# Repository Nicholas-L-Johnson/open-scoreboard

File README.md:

## Open Scoreboard

This project is a pocket scoreboard with Android/iOS/WatchOS apps.

The goal is a mass market product.  It beats out the existing devices on the market in features and price.

It really is small enough to fit in a pocket, and the battery lasts for up to 2 days of continuuous display on one charge.

It has some other modes too, a countdown timer and alarm clock

This project may be slightly doomed.  It will take about 35K to get the certifications, testing, and llc up to the level where these can be sold.  The real killer is the massive fee to use bluetooth.

I could seek a loan, but I am pretty against that at this point.  The app is not nearly ready, and it definitly needs to be migrated to a 4 layer board if I want to pass FCC testing.

Anyway, I'll keep working and maybe when it's ready there will be some cash I can spare on it.

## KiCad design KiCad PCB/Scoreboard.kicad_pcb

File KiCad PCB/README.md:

## PCB files

These are the hardware design files for the open scoreboard project.

The current design is based off of an nRF52833 with an RGB LED grid laid out as a scoreboard.

Version 0.1 controlled the LED's directly.  
This worked but required many pins and led to flickering and ghosting and lacked some creature comforts such as recharchable battery. 4 LEDs per segment also did not look great.

Version 0.2 attepted to switch to WLEDs.
This pulled far too much current and created heat problems. Battery charging and the larger NFC antenna were a success though.

The current version, 0.3 goes back to normal LEDs, but passes the control off to an LED grid controller. With lipo battery, improved NFC, Piezo, USB, 5 LED segments, and lower part count.

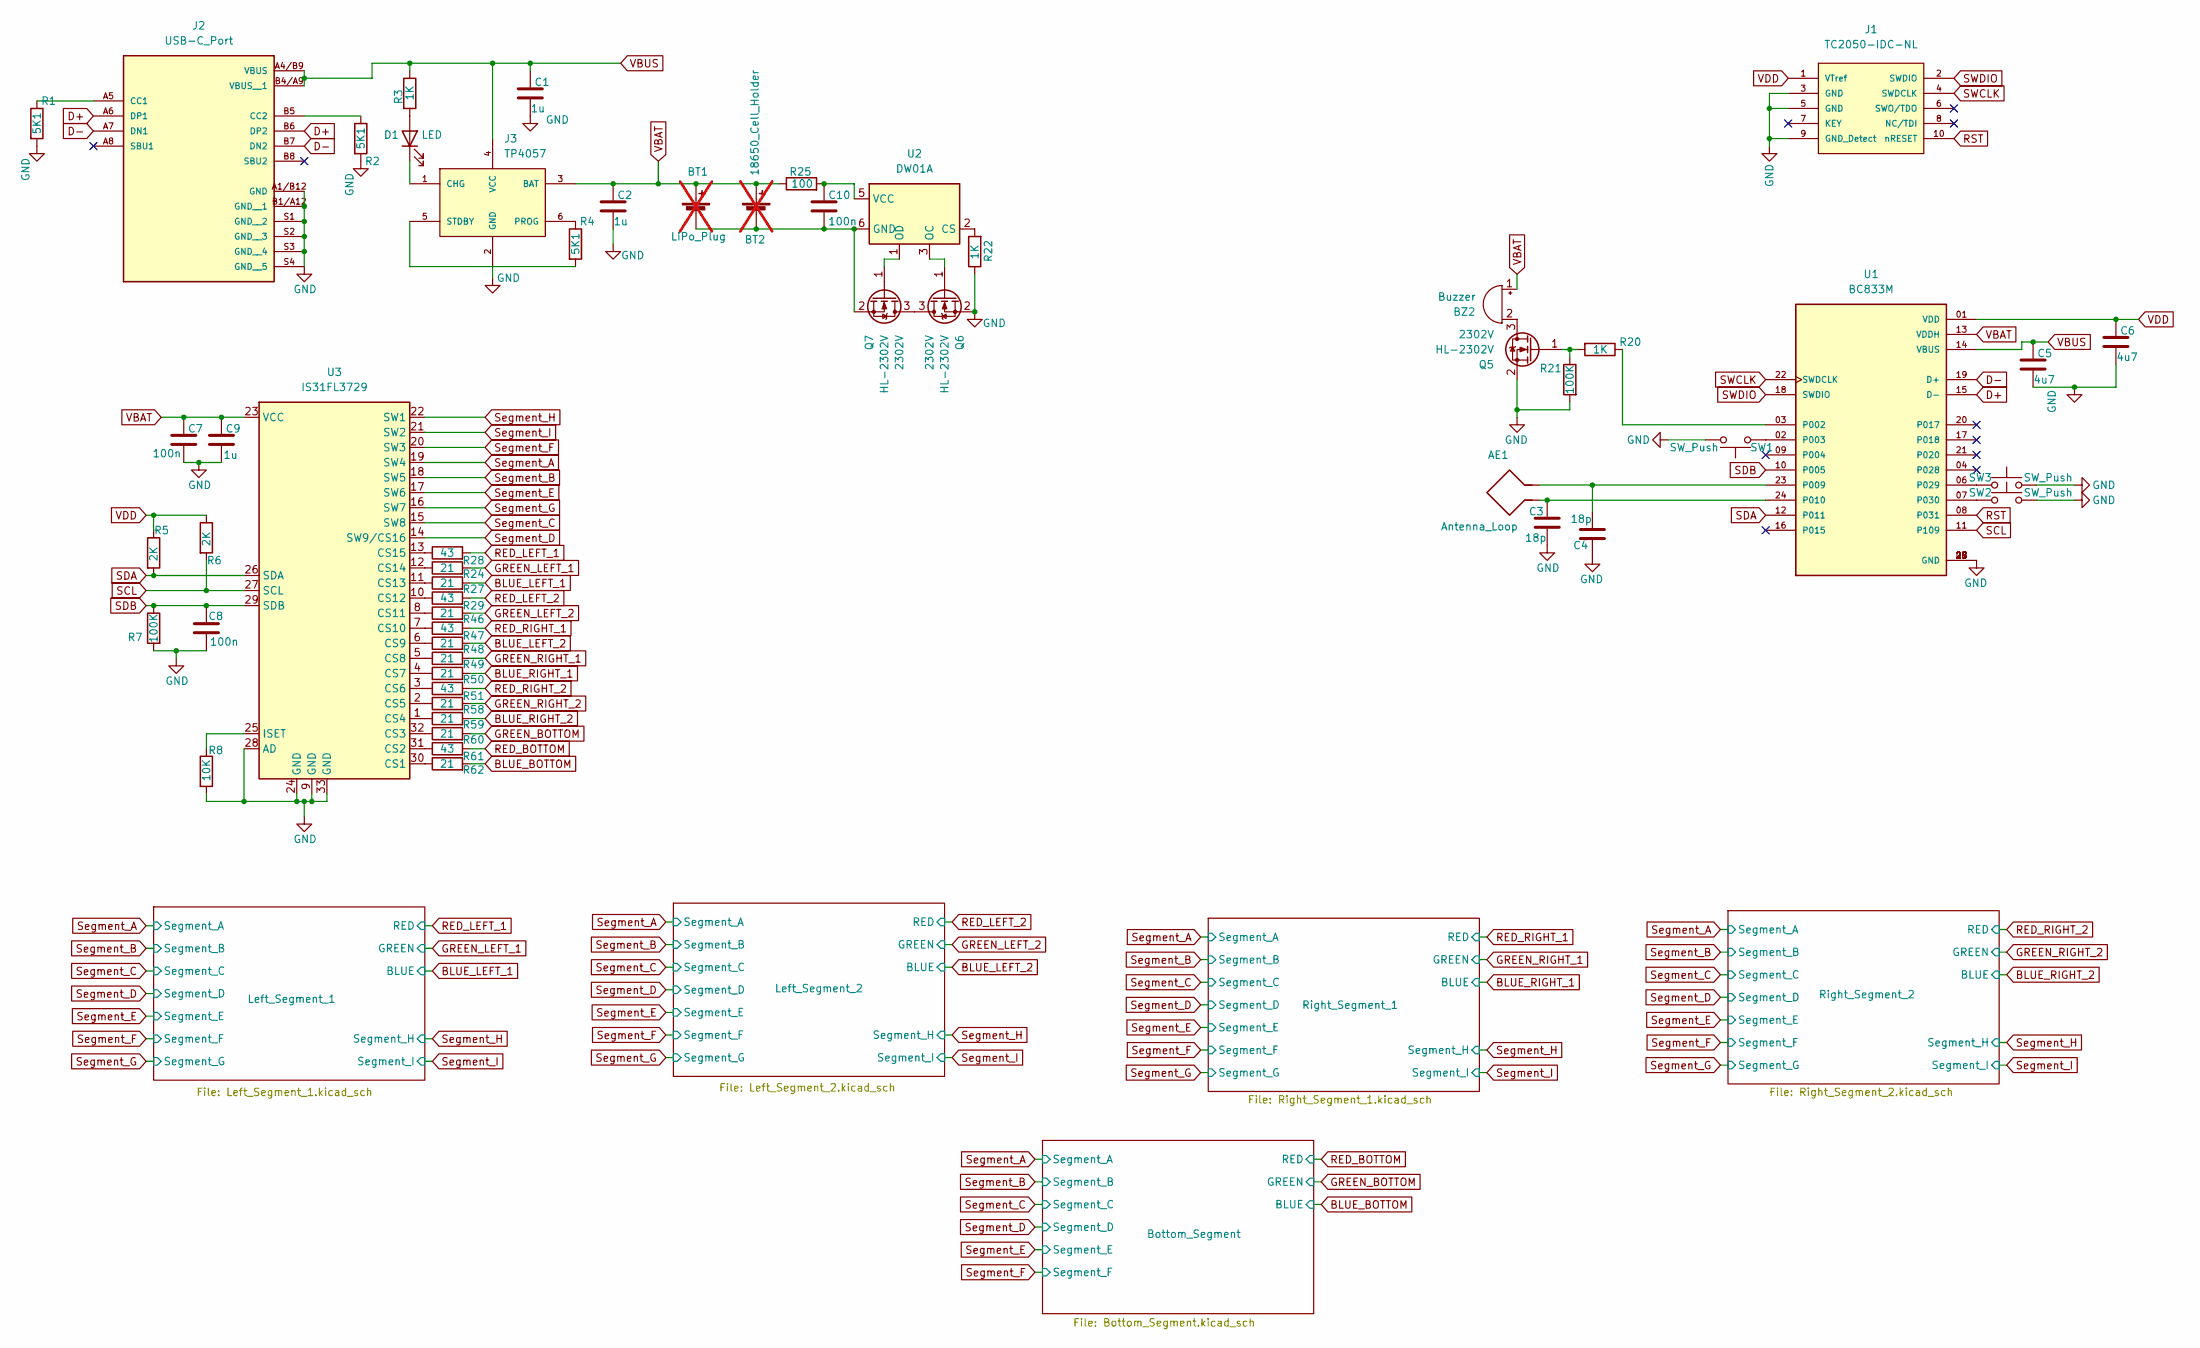
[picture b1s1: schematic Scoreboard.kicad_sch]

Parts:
AE1: Antenna_Loop; HM-NFC-Class3-Antenna
BT1: LiPo_Plug; JST_PH_S2B-PH-K_1x02_P2.00mm_Horizontal; Part Number WAFER-PH2.0-2PWB; LCSC Part Number C3029440; not fitted
BT2: 18650_Cell_Holder; Part Number BH-18650-A1AJ005; LCSC Part Number C5290176; not fitted
BZ2: Buzzer; XDCR_CMT-7525-80-SMT-TR; Part Number KLJ-7525-3627; LCSC Part Number C189208
C1, C2, C9: 1u; C_0603_1608Metric; Part Number CL10A105KO8NNNC; LCSC Part Number C1592
C3, C4: 18p; C_0603_1608Metric; Part Number FCC0603N180J500CT; LCSC Part Number C5137620
C5, C6: 4u7; C_0603_1608Metric; Part Number CGA0603X5R475K6R3JT; LCSC Part Number C7503506
C7, C8, C10: 100n; C_0603_1608Metric; Part Number CL10B104KA8NNNC; LCSC Part Number C1590
D1: LED; LED_0603_1608Metric; Part Number XL-1608SURC-06; LCSC Part Number C965799
J1: TC2050-IDC-NL; TAG-CONNECT_TC2050-IDC-NL; Part Number TC2050-IDC
J2: USB-C_Port; GCT_USB4110GFA; Part Number GT-USB-7014A; LCSC Part Number C963371
J3: TP4057; SOT-23-6; Part Number TP4057; LCSC Part Number C20199358
Q5, Q6, Q7: HL-2302V; SOT-23; Part Number 2302V; LCSC Part Number C7431443
R1, R2, R4: 5K1; R_0603_1608Metric; Part Number RC0603FR-075K1L; LCSC Part Number C105580
R3, R20, R22: 1K; R_0603_1608Metric; Part Number FRC0603J102 TS; LCSC Part Number C2907113
R5, R6: 2K; R_0603_1608Metric; Part Number FRC0603J202 TS; LCSC Part Number C2907137
R7, R21: 100K; R_0603_1608Metric; Part Number FRC0603J104 TS; LCSC Part Number C2907088
R8: 10K; R_0603_1608Metric; Part Number FRC0603J103 TS; LCSC Part Number C2930027
R24, R27, R46, R48, R49, R50, R58, R59, R60, R62: 21; R_0603_1608Metric; Part Number FRC0603F21R0TS; LCSC Part Number C5713281
R25: 100; R_0603_1608Metric; Part Number FRC0603J101 TS; LCSC Part Number C2907089
R28, R29, R47, R51, R61: 43; R_0603_1608Metric; Part Number FRC0603F43R0TS; LCSC Part Number C2907039
SW1, SW2, SW3: SW_Push; SW4_1437565_TEC; Part Number TS-1187A-C-D-B; LCSC Part Number C318888
U1: BC833M; XCVR_BC833M; Part Number BC833M
U2: DW01A; SOT-23-6; Part Number DW01A; LCSC Part Number C42380662
U3: IS31FL3729; QFN-32-1EP_4x4mm_P0.4mm_EP2.9x2.9mm_ThermalVias; Part Number IS31FL3729-QFLS4-TR; LCSC Part Number C2940549

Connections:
BLUE_BOTTOM: R62.2; also elsewhere on the board
BLUE_LEFT_1: R27.2; also elsewhere on the board
BLUE_LEFT_2: R48.2; also elsewhere on the board
BLUE_RIGHT_1: R50.2; also elsewhere on the board
BLUE_RIGHT_2: R59.2; also elsewhere on the board
D+: J2.A6 (DP1), J2.B6 (DP2), U1.15 (D-)
D-: J2.A7 (DN1), J2.B7 (DN2), U1.19 (D+)
GND: C1.2, C2.2, C3.2, C4.1, C5.2, C6.2, C7.2, C8.2, C9.2, J1.3 (GND), J1.5 (GND), J1.9 (GND_Detect), J2.A1/B12 (GND), J2.B1/A12 (GND__1), J2.S1 (GND__2), J2.S2 (GND__3), J2.S3 (GND__4), J2.S4 (GND__5), J3.2 (GND), Q5.2 (S), Q6.2 (S), R1.2, R2.2, R7.2, R8.2, R21.2, R22.1, SW1.1, SW2.1, SW3.1, U1.05 (GND), U1.25 (GND), U1.26 (GND), U1.27 (GND), U1.28 (GND), U3.9 (GND), U3.24 (GND), U3.28 (AD), U3.33 (GND)
GREEN_BOTTOM: R60.2; also elsewhere on the board
GREEN_LEFT_1: R24.2; also elsewhere on the board
GREEN_LEFT_2: R46.2; also elsewhere on the board
GREEN_RIGHT_1: R49.2; also elsewhere on the board
GREEN_RIGHT_2: R58.2; also elsewhere on the board
unnamed: BT1.2 (-), BT2.2 (-), C10.2, Q7.2 (S), U2.6 (GND)
unnamed: BZ2.2 (-), Q5.3 (D)
unnamed: D1.2 (A), R3.2
unnamed: D1.1 (K), J3.1 (CHG)
unnamed: J2.A5 (CC1), R1.1
unnamed: J2.B5 (CC2), R2.1
unnamed: J3.6 (PROG), R4.1
unnamed: J3.5 (STDBY), R4.2
unnamed: Q5.1 (G), R20.2, R21.1
unnamed: Q6.3 (D), Q7.3 (D)
unnamed: Q6.1 (G), U2.3 (OC)
unnamed: Q7.1 (G), U2.1 (OD)
unnamed: R20.1, U1.03 (P002)
unnamed: SW1.2, U1.02 (P003)
unnamed: AE1.2, C4.2, U1.23 (P009)
unnamed: AE1.1, C3.1, U1.24 (P010)
unnamed: SW3.2, U1.06 (P029)
unnamed: SW2.2, U1.07 (P030)
unnamed: R22.2, U2.2 (CS)
unnamed: C10.1, R25.2, U2.5 (VCC)
unnamed: R62.1, U3.30 (CS1)
unnamed: R61.1, U3.31 (CS2)
unnamed: R60.1, U3.32 (CS3)
unnamed: R59.1, U3.1 (CS4)
unnamed: R58.1, U3.2 (CS5)
unnamed: R51.1, U3.3 (CS6)
unnamed: R50.1, U3.4 (CS7)
unnamed: R49.1, U3.5 (CS8)
unnamed: R48.1, U3.6 (CS9)
unnamed: R47.1, U3.7 (CS10)
unnamed: R46.1, U3.8 (CS11)
unnamed: R29.1, U3.10 (CS12)
unnamed: R27.1, U3.11 (CS13)
unnamed: R24.1, U3.12 (CS14)
unnamed: R28.1, U3.13 (CS15)
unnamed: R8.1, U3.25 (ISET)
RED_BOTTOM: R61.2; also elsewhere on the board
RED_LEFT_1: R28.2; also elsewhere on the board
RED_LEFT_2: R29.2; also elsewhere on the board
RED_RIGHT_1: R47.2; also elsewhere on the board
RED_RIGHT_2: R51.2; also elsewhere on the board
RST: J1.10 (nRESET), U1.08 (P031)
SCL: R6.2, U1.11 (P109), U3.27 (SCL)
SDA: R5.2, U1.12 (P011), U3.26 (SDA)
SDB: C8.1, R7.1, U1.10 (P005), U3.29 (SDB)
SWCLK: J1.4 (SWDCLK), U1.22 (SWDCLK)
SWDIO: J1.2 (SWDIO), U1.18 (SWDIO)
Segment_A: U3.19 (SW4); also elsewhere on the board
Segment_B: U3.18 (SW5); also elsewhere on the board
Segment_C: U3.15 (SW8); also elsewhere on the board
Segment_D: U3.14 (SW9/CS16); also elsewhere on the board
Segment_E: U3.17 (SW6); also elsewhere on the board
Segment_F: U3.20 (SW3); also elsewhere on the board
Segment_G: U3.16 (SW7); also elsewhere on the board
Segment_H: U3.22 (SW1); also elsewhere on the board
Segment_I: U3.21 (SW2); also elsewhere on the board
VBAT: BT1.1 (+), BT2.1 (+), BZ2.1 (+), C2.1, C7.1, C9.1, J3.3 (BAT), R25.1, U1.13 (VDDH), U3.23 (VCC)
VBUS: C1.1, C5.1, J2.A4/B9 (VBUS), J2.B4/A9 (VBUS__1), J3.4 (VCC), R3.1, U1.14 (VBUS)
VDD: C6.1, J1.1 (VTref), R5.1, R6.1, U1.01 (VDD)

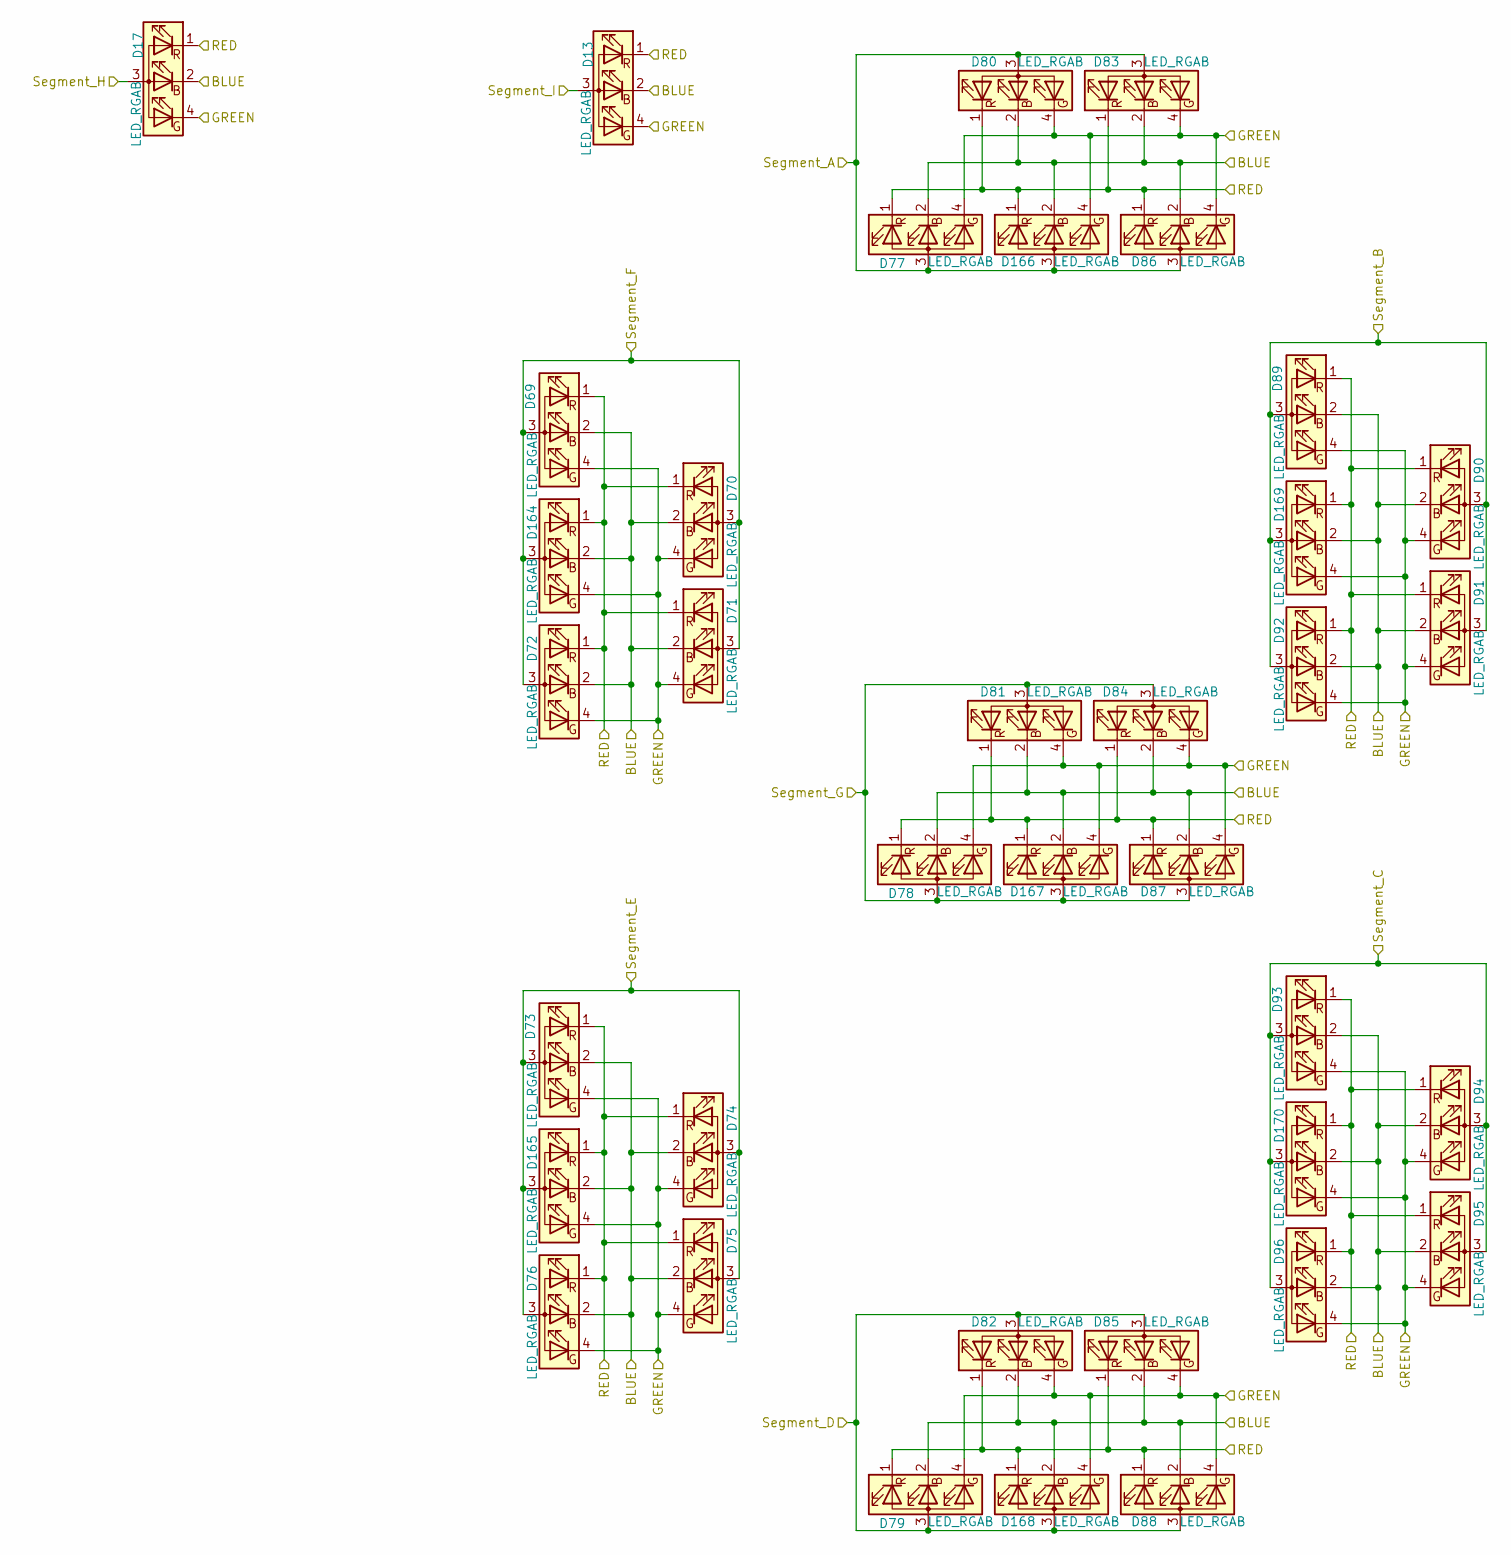
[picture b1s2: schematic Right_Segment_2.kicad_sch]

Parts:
D13, D17, D69, D70, D71, D72, D73, D74, D75, D76, D77, D78, D79, D80, D81, D82, D83, D84, D85, D86, D87, D88, D89, D90, D91, D92, D93, D94, D95, D96, D164, D165, D166, D167, D168, D169, D170: LED_RGAB; RGB_LED_NH-B2020RGBA-HF; Part Number NH-B2020RGBA-HF; LCSC Part Number C2874116

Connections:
BLUE_RIGHT_2: D13.2 (GK), D17.2 (GK), D69.2 (GK), D70.2 (GK), D71.2 (GK), D72.2 (GK), D73.2 (GK), D74.2 (GK), D75.2 (GK), D76.2 (GK), D77.2 (GK), D78.2 (GK), D79.2 (GK), D80.2 (GK), D81.2 (GK), D82.2 (GK), D83.2 (GK), D84.2 (GK), D85.2 (GK), D86.2 (GK), D87.2 (GK), D88.2 (GK), D89.2 (GK), D90.2 (GK), D91.2 (GK), D92.2 (GK), D93.2 (GK), D94.2 (GK), D95.2 (GK), D96.2 (GK), D164.2 (GK), D165.2 (GK), D166.2 (GK), D167.2 (GK), D168.2 (GK), D169.2 (GK), D170.2 (GK); also elsewhere on the board
GREEN_RIGHT_2: D13.4 (BK), D17.4 (BK), D69.4 (BK), D70.4 (BK), D71.4 (BK), D72.4 (BK), D73.4 (BK), D74.4 (BK), D75.4 (BK), D76.4 (BK), D77.4 (BK), D78.4 (BK), D79.4 (BK), D80.4 (BK), D81.4 (BK), D82.4 (BK), D83.4 (BK), D84.4 (BK), D85.4 (BK), D86.4 (BK), D87.4 (BK), D88.4 (BK), D89.4 (BK), D90.4 (BK), D91.4 (BK), D92.4 (BK), D93.4 (BK), D94.4 (BK), D95.4 (BK), D96.4 (BK), D164.4 (BK), D165.4 (BK), D166.4 (BK), D167.4 (BK), D168.4 (BK), D169.4 (BK), D170.4 (BK); also elsewhere on the board
RED_RIGHT_2: D13.1 (RK), D17.1 (RK), D69.1 (RK), D70.1 (RK), D71.1 (RK), D72.1 (RK), D73.1 (RK), D74.1 (RK), D75.1 (RK), D76.1 (RK), D77.1 (RK), D78.1 (RK), D79.1 (RK), D80.1 (RK), D81.1 (RK), D82.1 (RK), D83.1 (RK), D84.1 (RK), D85.1 (RK), D86.1 (RK), D87.1 (RK), D88.1 (RK), D89.1 (RK), D90.1 (RK), D91.1 (RK), D92.1 (RK), D93.1 (RK), D94.1 (RK), D95.1 (RK), D96.1 (RK), D164.1 (RK), D165.1 (RK), D166.1 (RK), D167.1 (RK), D168.1 (RK), D169.1 (RK), D170.1 (RK); also elsewhere on the board
Segment_A: D77.3 (A), D80.3 (A), D83.3 (A), D86.3 (A), D166.3 (A); also elsewhere on the board
Segment_B: D89.3 (A), D90.3 (A), D91.3 (A), D92.3 (A), D169.3 (A); also elsewhere on the board
Segment_C: D93.3 (A), D94.3 (A), D95.3 (A), D96.3 (A), D170.3 (A); also elsewhere on the board
Segment_D: D79.3 (A), D82.3 (A), D85.3 (A), D88.3 (A), D168.3 (A); also elsewhere on the board
Segment_E: D73.3 (A), D74.3 (A), D75.3 (A), D76.3 (A), D165.3 (A); also elsewhere on the board
Segment_F: D69.3 (A), D70.3 (A), D71.3 (A), D72.3 (A), D164.3 (A); also elsewhere on the board
Segment_G: D78.3 (A), D81.3 (A), D84.3 (A), D87.3 (A), D167.3 (A); also elsewhere on the board
Segment_H: D17.3 (A); also elsewhere on the board
Segment_I: D13.3 (A); also elsewhere on the board

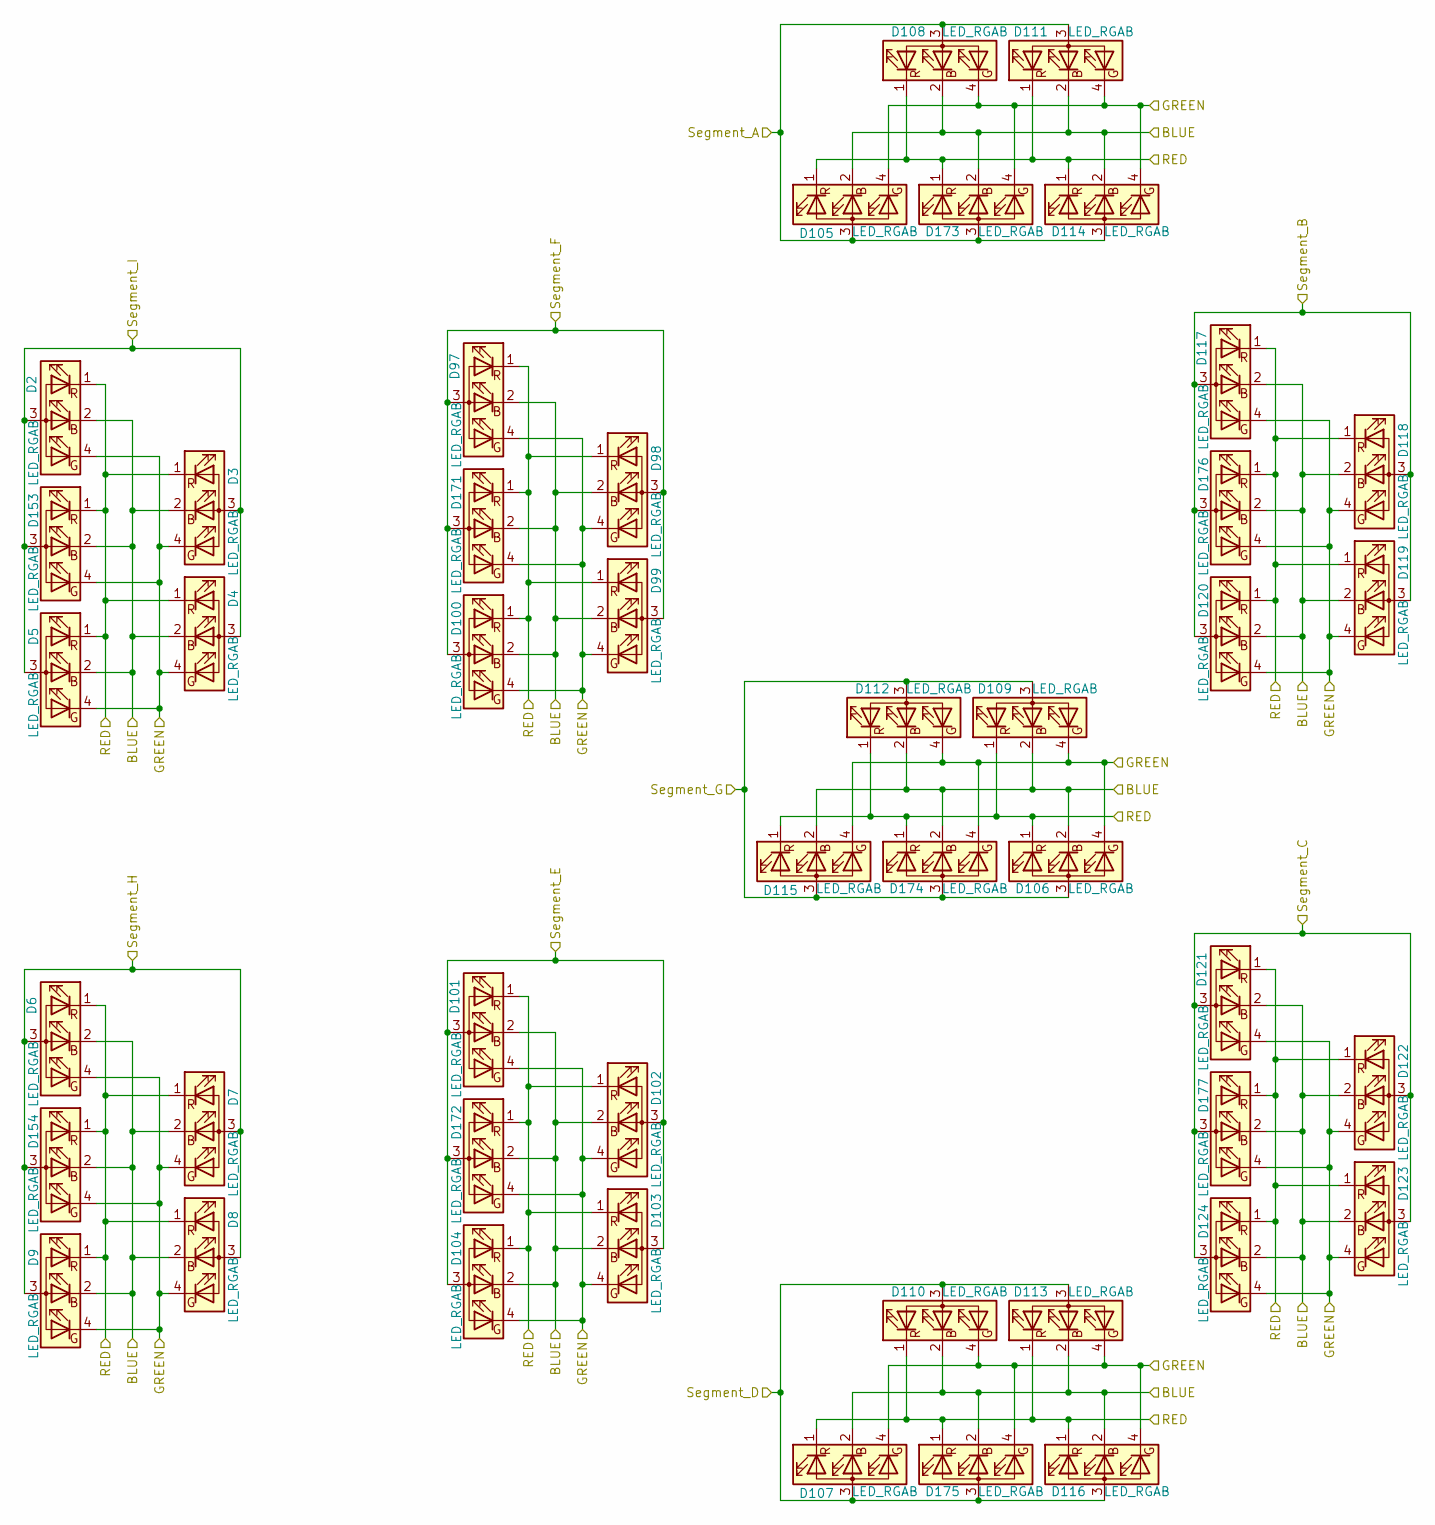
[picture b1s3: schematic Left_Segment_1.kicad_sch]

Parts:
D2, D3, D4, D5, D6, D7, D8, D9, D97, D98, D99, D100, D101, D102, D103, D104, D105, D106, D107, D108, D109, D110, D111, D112, D113, D114, D115, D116, D117, D118, D119, D120, D121, D122, D123, D124, D153, D154, D171, D172, D173, D174, D175, D176, D177: LED_RGAB; RGB_LED_NH-B2020RGBA-HF; Part Number NH-B2020RGBA-HF; LCSC Part Number C2874116

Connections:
BLUE_LEFT_1: D2.2 (GK), D3.2 (GK), D4.2 (GK), D5.2 (GK), D6.2 (GK), D7.2 (GK), D8.2 (GK), D9.2 (GK), D97.2 (GK), D98.2 (GK), D99.2 (GK), D100.2 (GK), D101.2 (GK), D102.2 (GK), D103.2 (GK), D104.2 (GK), D105.2 (GK), D106.2 (GK), D107.2 (GK), D108.2 (GK), D109.2 (GK), D110.2 (GK), D111.2 (GK), D112.2 (GK), D113.2 (GK), D114.2 (GK), D115.2 (GK), D116.2 (GK), D117.2 (GK), D118.2 (GK), D119.2 (GK), D120.2 (GK), D121.2 (GK), D122.2 (GK), D123.2 (GK), D124.2 (GK), D153.2 (GK), D154.2 (GK), D171.2 (GK), D172.2 (GK), D173.2 (GK), D174.2 (GK), D175.2 (GK), D176.2 (GK), D177.2 (GK); also elsewhere on the board
GREEN_LEFT_1: D2.4 (BK), D3.4 (BK), D4.4 (BK), D5.4 (BK), D6.4 (BK), D7.4 (BK), D8.4 (BK), D9.4 (BK), D97.4 (BK), D98.4 (BK), D99.4 (BK), D100.4 (BK), D101.4 (BK), D102.4 (BK), D103.4 (BK), D104.4 (BK), D105.4 (BK), D106.4 (BK), D107.4 (BK), D108.4 (BK), D109.4 (BK), D110.4 (BK), D111.4 (BK), D112.4 (BK), D113.4 (BK), D114.4 (BK), D115.4 (BK), D116.4 (BK), D117.4 (BK), D118.4 (BK), D119.4 (BK), D120.4 (BK), D121.4 (BK), D122.4 (BK), D123.4 (BK), D124.4 (BK), D153.4 (BK), D154.4 (BK), D171.4 (BK), D172.4 (BK), D173.4 (BK), D174.4 (BK), D175.4 (BK), D176.4 (BK), D177.4 (BK); also elsewhere on the board
RED_LEFT_1: D2.1 (RK), D3.1 (RK), D4.1 (RK), D5.1 (RK), D6.1 (RK), D7.1 (RK), D8.1 (RK), D9.1 (RK), D97.1 (RK), D98.1 (RK), D99.1 (RK), D100.1 (RK), D101.1 (RK), D102.1 (RK), D103.1 (RK), D104.1 (RK), D105.1 (RK), D106.1 (RK), D107.1 (RK), D108.1 (RK), D109.1 (RK), D110.1 (RK), D111.1 (RK), D112.1 (RK), D113.1 (RK), D114.1 (RK), D115.1 (RK), D116.1 (RK), D117.1 (RK), D118.1 (RK), D119.1 (RK), D120.1 (RK), D121.1 (RK), D122.1 (RK), D123.1 (RK), D124.1 (RK), D153.1 (RK), D154.1 (RK), D171.1 (RK), D172.1 (RK), D173.1 (RK), D174.1 (RK), D175.1 (RK), D176.1 (RK), D177.1 (RK); also elsewhere on the board
Segment_A: D105.3 (A), D108.3 (A), D111.3 (A), D114.3 (A), D173.3 (A); also elsewhere on the board
Segment_B: D117.3 (A), D118.3 (A), D119.3 (A), D120.3 (A), D176.3 (A); also elsewhere on the board
Segment_C: D121.3 (A), D122.3 (A), D123.3 (A), D124.3 (A), D177.3 (A); also elsewhere on the board
Segment_D: D107.3 (A), D110.3 (A), D113.3 (A), D116.3 (A), D175.3 (A); also elsewhere on the board
Segment_E: D101.3 (A), D102.3 (A), D103.3 (A), D104.3 (A), D172.3 (A); also elsewhere on the board
Segment_F: D97.3 (A), D98.3 (A), D99.3 (A), D100.3 (A), D171.3 (A); also elsewhere on the board
Segment_G: D106.3 (A), D109.3 (A), D112.3 (A), D115.3 (A), D174.3 (A); also elsewhere on the board
Segment_H: D6.3 (A), D7.3 (A), D8.3 (A), D9.3 (A), D154.3 (A); also elsewhere on the board
Segment_I: D2.3 (A), D3.3 (A), D4.3 (A), D5.3 (A), D153.3 (A); also elsewhere on the board

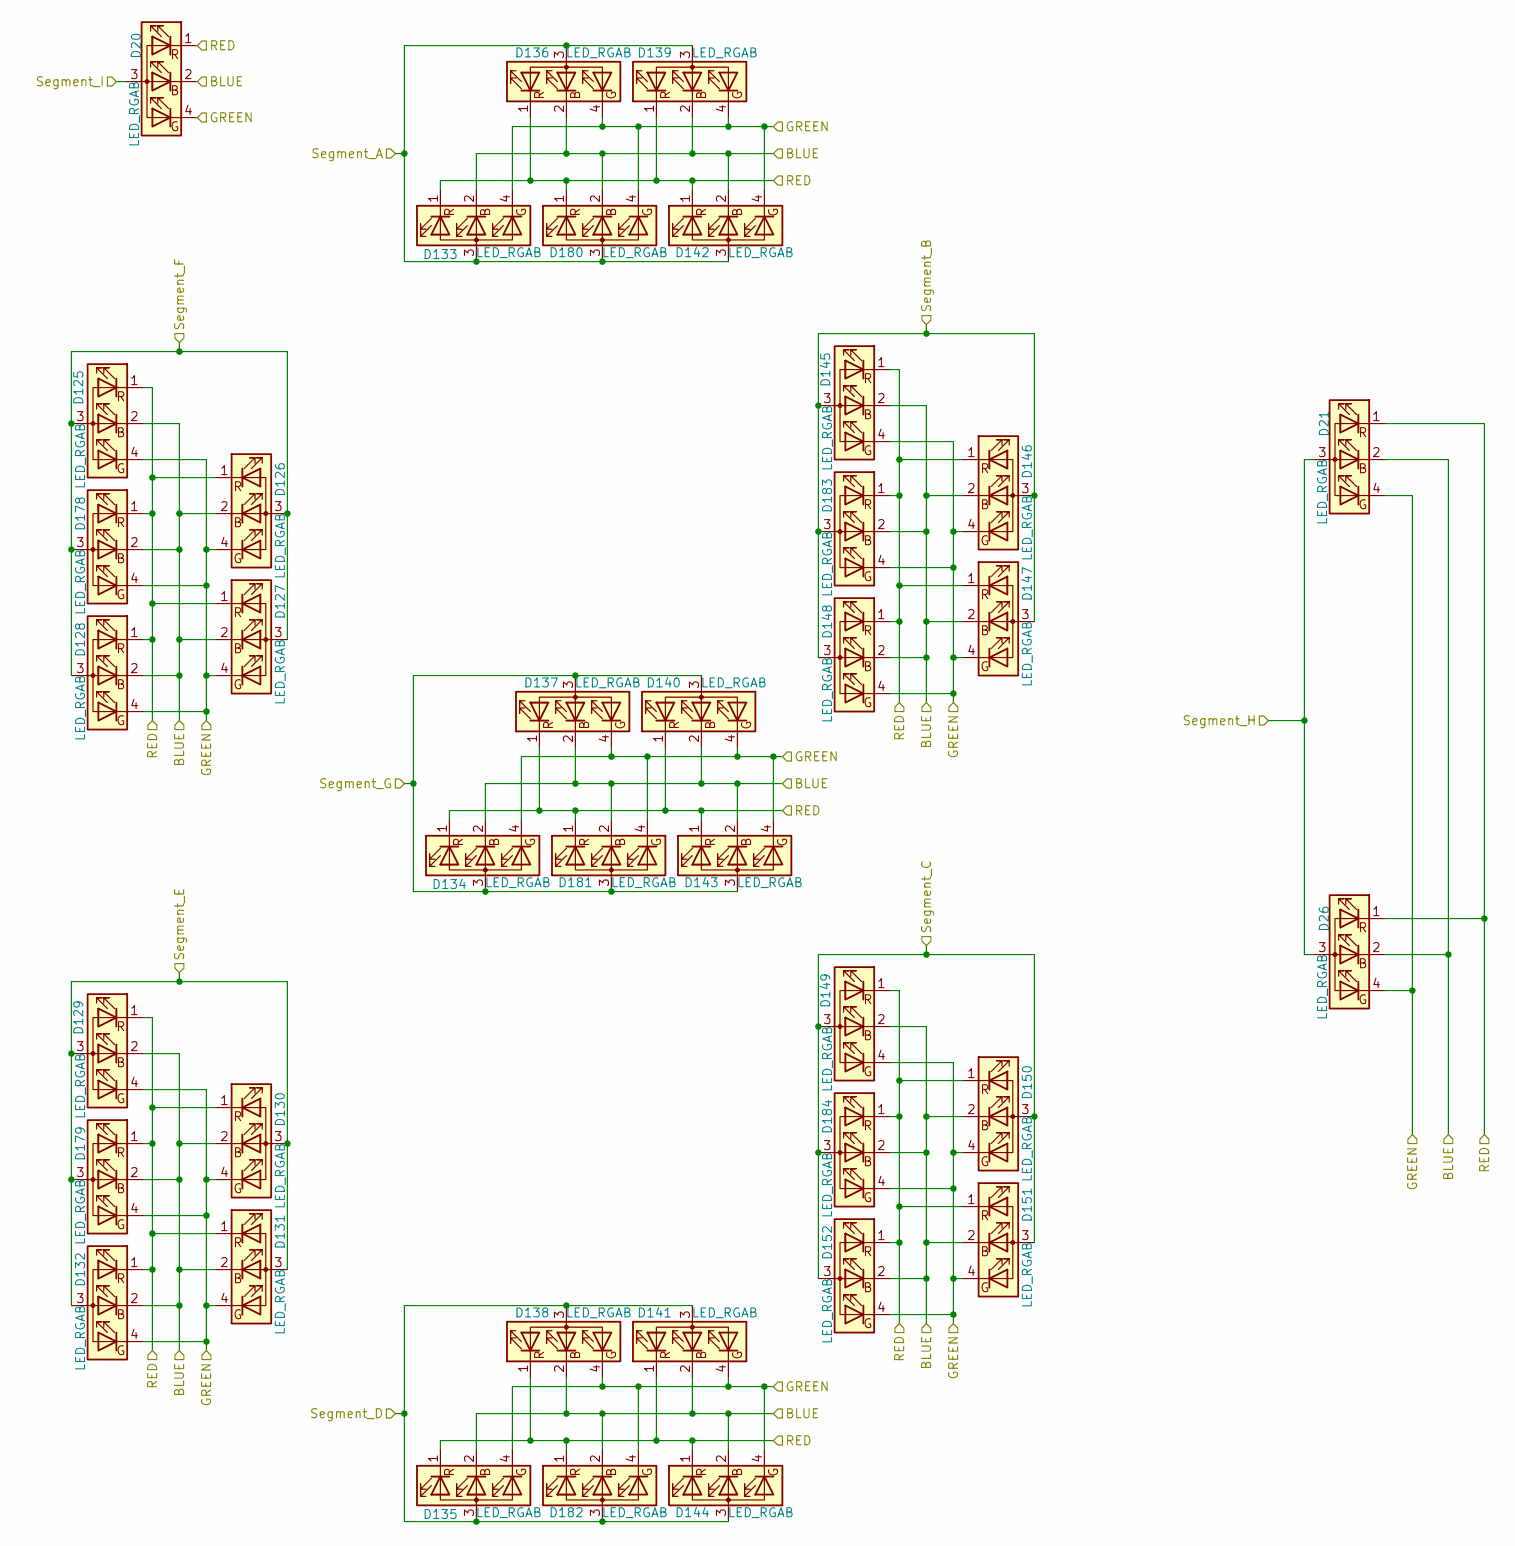
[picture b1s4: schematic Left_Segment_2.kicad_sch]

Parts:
D20, D21, D26, D125, D126, D127, D128, D129, D130, D131, D132, D133, D134, D135, D136, D137, D138, D139, D140, D141, D142, D143, D144, D145, D146, D147, D148, D149, D150, D151, D152, D178, D179, D180, D181, D182, D183, D184: LED_RGAB; RGB_LED_NH-B2020RGBA-HF; Part Number NH-B2020RGBA-HF; LCSC Part Number C2874116

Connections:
BLUE_LEFT_2: D20.2 (GK), D21.2 (GK), D26.2 (GK), D125.2 (GK), D126.2 (GK), D127.2 (GK), D128.2 (GK), D129.2 (GK), D130.2 (GK), D131.2 (GK), D132.2 (GK), D133.2 (GK), D134.2 (GK), D135.2 (GK), D136.2 (GK), D137.2 (GK), D138.2 (GK), D139.2 (GK), D140.2 (GK), D141.2 (GK), D142.2 (GK), D143.2 (GK), D144.2 (GK), D145.2 (GK), D146.2 (GK), D147.2 (GK), D148.2 (GK), D149.2 (GK), D150.2 (GK), D151.2 (GK), D152.2 (GK), D178.2 (GK), D179.2 (GK), D180.2 (GK), D181.2 (GK), D182.2 (GK), D183.2 (GK), D184.2 (GK); also elsewhere on the board
GREEN_LEFT_2: D20.4 (BK), D21.4 (BK), D26.4 (BK), D125.4 (BK), D126.4 (BK), D127.4 (BK), D128.4 (BK), D129.4 (BK), D130.4 (BK), D131.4 (BK), D132.4 (BK), D133.4 (BK), D134.4 (BK), D135.4 (BK), D136.4 (BK), D137.4 (BK), D138.4 (BK), D139.4 (BK), D140.4 (BK), D141.4 (BK), D142.4 (BK), D143.4 (BK), D144.4 (BK), D145.4 (BK), D146.4 (BK), D147.4 (BK), D148.4 (BK), D149.4 (BK), D150.4 (BK), D151.4 (BK), D152.4 (BK), D178.4 (BK), D179.4 (BK), D180.4 (BK), D181.4 (BK), D182.4 (BK), D183.4 (BK), D184.4 (BK); also elsewhere on the board
RED_LEFT_2: D20.1 (RK), D21.1 (RK), D26.1 (RK), D125.1 (RK), D126.1 (RK), D127.1 (RK), D128.1 (RK), D129.1 (RK), D130.1 (RK), D131.1 (RK), D132.1 (RK), D133.1 (RK), D134.1 (RK), D135.1 (RK), D136.1 (RK), D137.1 (RK), D138.1 (RK), D139.1 (RK), D140.1 (RK), D141.1 (RK), D142.1 (RK), D143.1 (RK), D144.1 (RK), D145.1 (RK), D146.1 (RK), D147.1 (RK), D148.1 (RK), D149.1 (RK), D150.1 (RK), D151.1 (RK), D152.1 (RK), D178.1 (RK), D179.1 (RK), D180.1 (RK), D181.1 (RK), D182.1 (RK), D183.1 (RK), D184.1 (RK); also elsewhere on the board
Segment_A: D133.3 (A), D136.3 (A), D139.3 (A), D142.3 (A), D180.3 (A); also elsewhere on the board
Segment_B: D145.3 (A), D146.3 (A), D147.3 (A), D148.3 (A), D183.3 (A); also elsewhere on the board
Segment_C: D149.3 (A), D150.3 (A), D151.3 (A), D152.3 (A), D184.3 (A); also elsewhere on the board
Segment_D: D135.3 (A), D138.3 (A), D141.3 (A), D144.3 (A), D182.3 (A); also elsewhere on the board
Segment_E: D129.3 (A), D130.3 (A), D131.3 (A), D132.3 (A), D179.3 (A); also elsewhere on the board
Segment_F: D125.3 (A), D126.3 (A), D127.3 (A), D128.3 (A), D178.3 (A); also elsewhere on the board
Segment_G: D134.3 (A), D137.3 (A), D140.3 (A), D143.3 (A), D181.3 (A); also elsewhere on the board
Segment_H: D21.3 (A), D26.3 (A); also elsewhere on the board
Segment_I: D20.3 (A); also elsewhere on the board

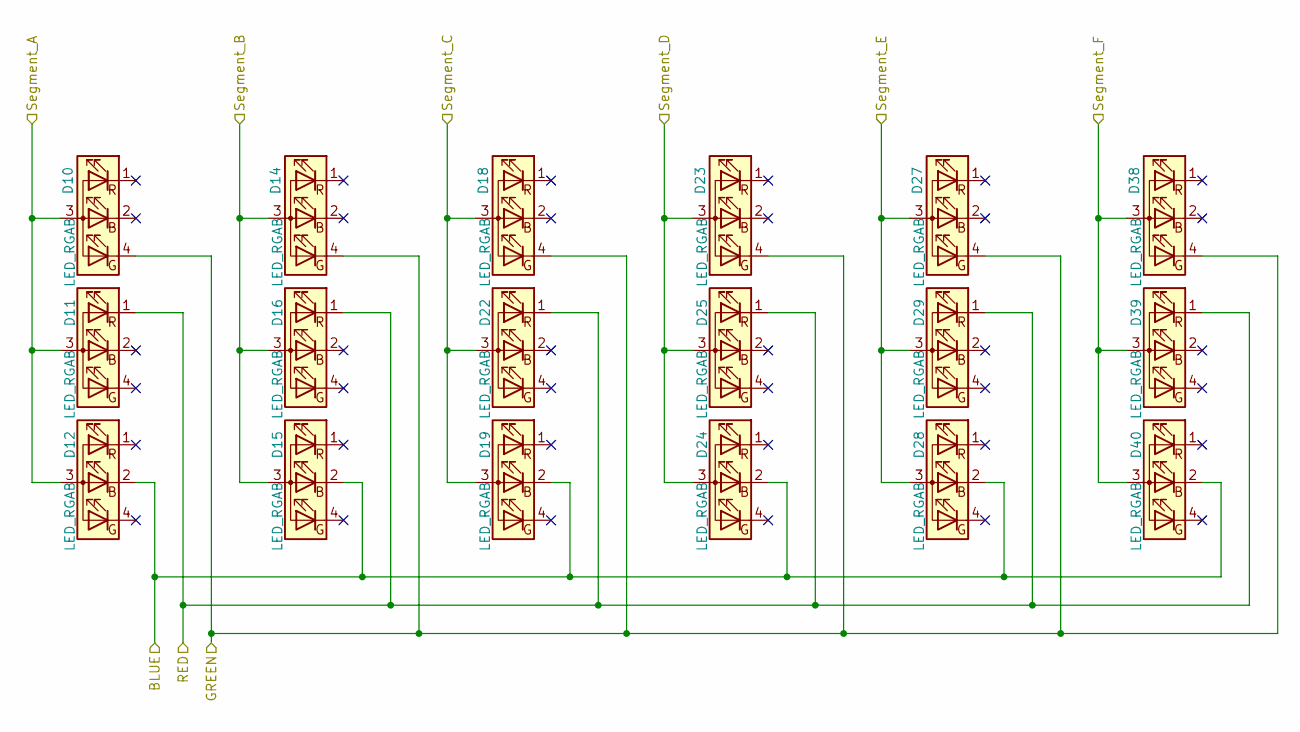
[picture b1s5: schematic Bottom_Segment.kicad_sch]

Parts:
D10, D11, D12, D14, D15, D16, D18, D19, D22, D23, D24, D25, D27, D28, D29, D38, D39, D40: LED_RGAB; RGB_LED_NH-B2020RGBA-HF; Part Number NH-B2020RGBA-HF; LCSC Part Number C2874116

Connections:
BLUE_BOTTOM: D12.2 (GK), D15.2 (GK), D19.2 (GK), D24.2 (GK), D28.2 (GK), D40.2 (GK); also elsewhere on the board
GREEN_BOTTOM: D10.4 (BK), D14.4 (BK), D18.4 (BK), D23.4 (BK), D27.4 (BK), D38.4 (BK); also elsewhere on the board
RED_BOTTOM: D11.1 (RK), D16.1 (RK), D22.1 (RK), D25.1 (RK), D29.1 (RK), D39.1 (RK); also elsewhere on the board
Segment_A: D10.3 (A), D11.3 (A), D12.3 (A); also elsewhere on the board
Segment_B: D14.3 (A), D15.3 (A), D16.3 (A); also elsewhere on the board
Segment_C: D18.3 (A), D19.3 (A), D22.3 (A); also elsewhere on the board
Segment_D: D23.3 (A), D24.3 (A), D25.3 (A); also elsewhere on the board
Segment_E: D27.3 (A), D28.3 (A), D29.3 (A); also elsewhere on the board
Segment_F: D38.3 (A), D39.3 (A), D40.3 (A); also elsewhere on the board
